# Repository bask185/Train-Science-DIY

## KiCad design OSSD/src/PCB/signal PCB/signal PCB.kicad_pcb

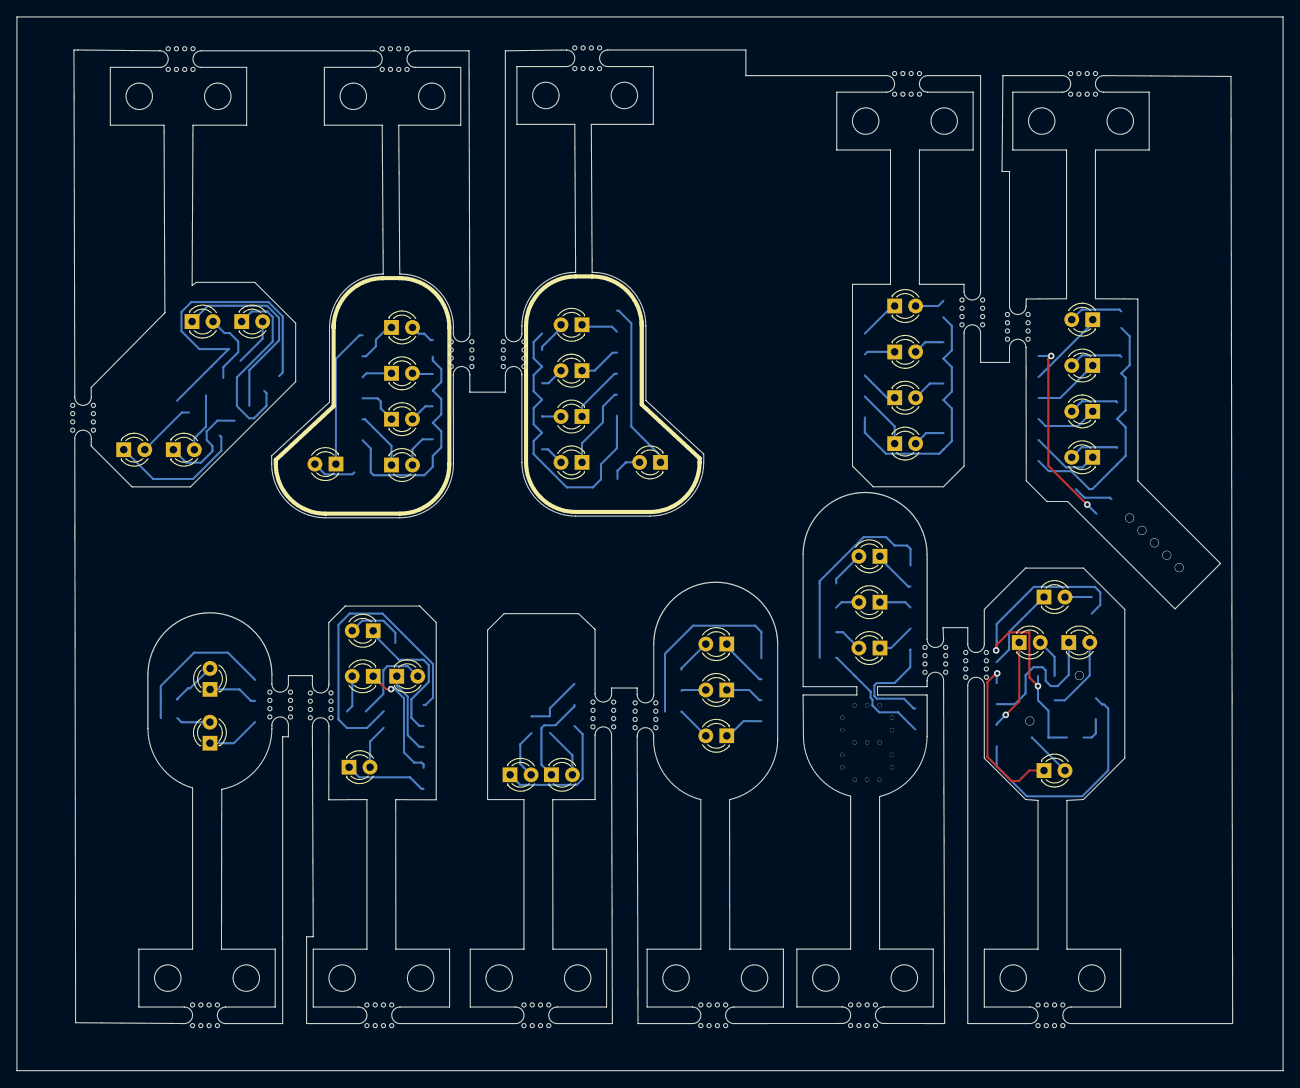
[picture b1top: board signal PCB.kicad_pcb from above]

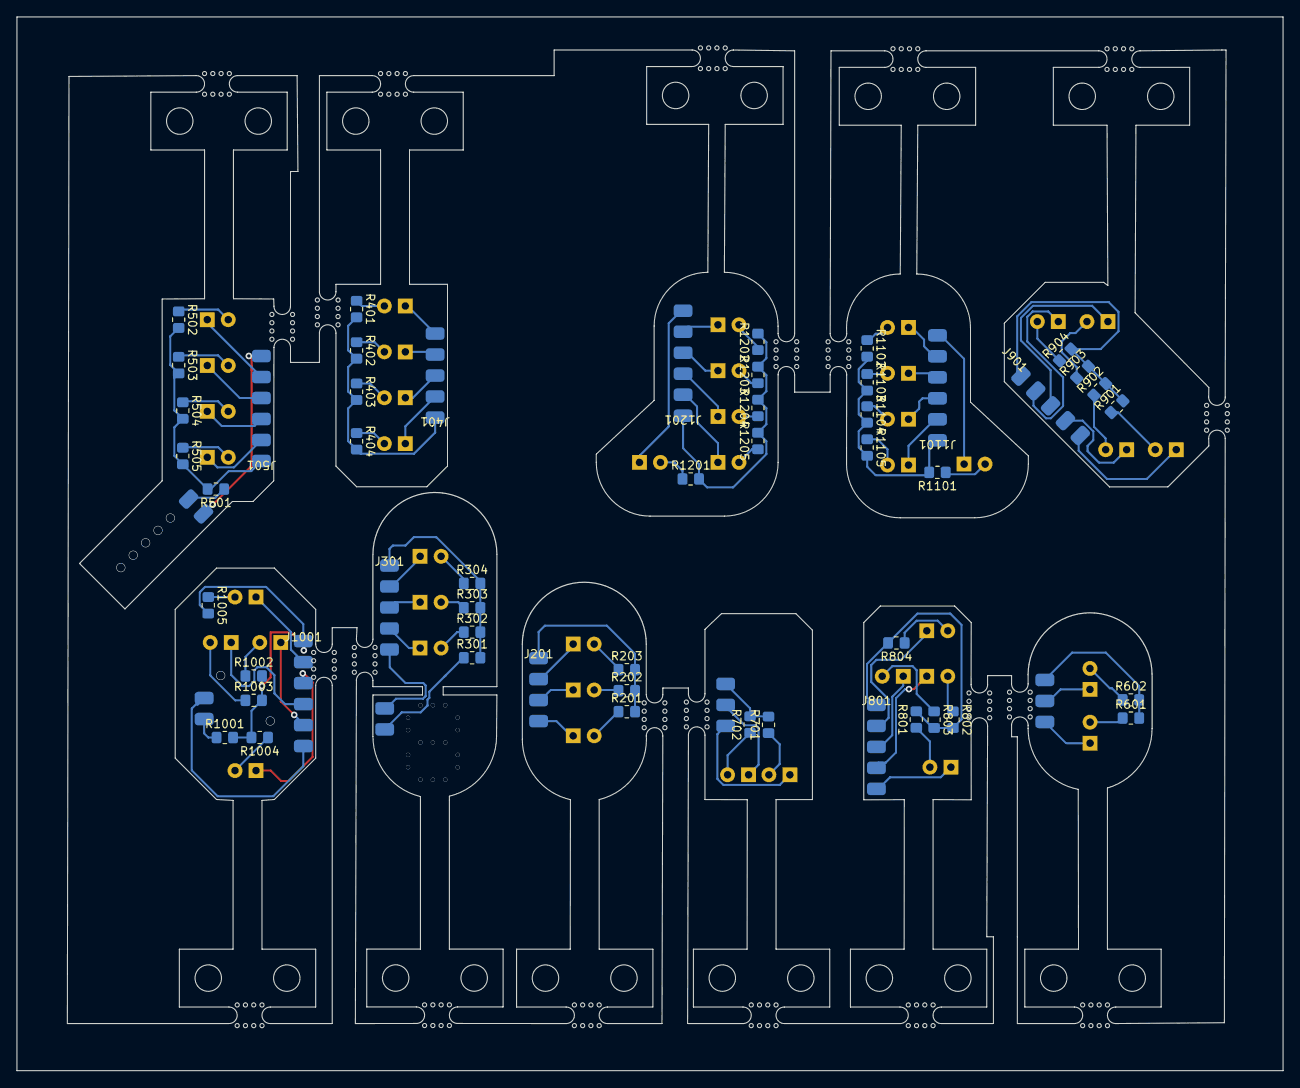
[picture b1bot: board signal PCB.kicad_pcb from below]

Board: 2 copper layers, 153.2 x 127.5 mm, 97 parts (57 on the bottom side), 97 nets.

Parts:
D201, D202, D203, D301, D302, D303, D401, D402, D403, D404, D501, D502, D503, D504, D601, D602, D701, D702, D801, D802, D803, D804, D901, D902, D903, D904, D1001, D1002, D1003, D1004, D1101, D1102, D1103, D1104, D1105, D1201, D1202, D1203, D1204, D1205: LED; LED_NO_SILK
D304, D505, D1005: LED; 02_solderpad_2.54
J201: Conn_01x04; 04_solderpad_2.54
J301, J401, J901: Conn_01x05; 05_solderpad_2.54
J501, J1001, J1101, J1201: Conn_01x06; 06_solderpad_2.54
J601, J701: Conn_01x04; 03_solderpad_2.54
J801: Conn_01x04; 05_solderpad_2.54
R201, R202, R203, R301, R302, R303, R304, R401, R402, R403, R404, R501, R502, R503, R504, R505, R601, R602, R701, R702, R801, R802, R803, R804, R901, R902, R903, R904, R1001, R1002, R1003, R1004, R1005, R1101, R1102, R1103, R1104, R1105, R1201, R1202, R1203, R1204, R1205: R; R_0805_2012Metric_Pad1.20x1.40mm_HandSolder

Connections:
unnamed: D201.2 (A), R203.1
unnamed: D201.1 (K), J201.2
unnamed: D202.2 (A), R202.1
unnamed: D202.1 (K), J201.3
unnamed: D203.2 (A), R201.1
unnamed: D203.1 (K), J201.4
unnamed: D301.2 (A), R304.1
unnamed: D301.1 (K), J301.2
unnamed: D302.2 (A), R303.1
unnamed: D302.1 (K), J301.3
unnamed: D303.2 (A), R302.1
unnamed: D303.1 (K), J301.4
unnamed: D304.2 (A), R301.1
unnamed: D304.1 (K), J301.5
unnamed: D401.2 (A), R404.1
unnamed: D401.1 (K), J401.2
unnamed: D402.2 (A), R403.1
unnamed: D402.1 (K), J401.3
unnamed: D403.2 (A), R402.1
unnamed: D403.1 (K), J401.4
unnamed: D404.2 (A), R401.1
unnamed: D404.1 (K), J401.5
unnamed: D501.2 (A), R505.1
unnamed: D501.1 (K), J501.2
unnamed: D502.2 (A), R504.1
unnamed: D502.1 (K), J501.3
unnamed: D503.2 (A), R503.1
unnamed: D503.1 (K), J501.4
unnamed: D504.2 (A), R502.1
unnamed: D504.1 (K), J501.5
unnamed: D505.2 (A), R501.1
unnamed: D505.1 (K), J501.6
unnamed: D601.2 (A), R602.1
unnamed: D601.1 (K), J601.2
unnamed: D602.2 (A), R601.1
unnamed: D602.1 (K), J601.3
unnamed: D701.2 (A), R702.1
unnamed: D701.1 (K), J701.2
unnamed: D702.2 (A), R701.1
unnamed: D702.1 (K), J701.3
unnamed: D801.2 (A), R804.1
unnamed: D801.1 (K), J801.2
unnamed: D802.2 (A), R803.1
unnamed: D802.1 (K), J801.3
unnamed: D803.2 (A), R802.1
unnamed: D803.1 (K), J801.4
unnamed: D804.2 (A), R801.1
unnamed: D804.1 (K), J801.5
unnamed: D901.2 (A), R904.1
unnamed: D901.1 (K), J901.2
unnamed: D902.2 (A), R903.1
unnamed: D902.1 (K), J901.3
unnamed: D903.2 (A), R902.1
unnamed: D903.1 (K), J901.4
unnamed: D904.2 (A), R901.1
unnamed: D904.1 (K), J901.5
unnamed: D1001.2 (A), R1005.1
unnamed: D1001.1 (K), J1001.2
unnamed: D1002.2 (A), R1004.1
unnamed: D1002.1 (K), J1001.3
unnamed: D1003.2 (A), R1003.1
unnamed: D1003.1 (K), J1001.4
unnamed: D1004.2 (A), R1002.1
unnamed: D1004.1 (K), J1001.5
unnamed: D1005.2 (A), R1001.1
unnamed: D1005.1 (K), J1001.6
unnamed: D1101.2 (A), R1105.1
unnamed: D1101.1 (K), J1101.2
unnamed: D1102.2 (A), R1104.1
unnamed: D1102.1 (K), J1101.3
unnamed: D1103.2 (A), R1103.1
unnamed: D1103.1 (K), J1101.4
unnamed: D1104.2 (A), R1102.1
unnamed: D1104.1 (K), J1101.5
unnamed: D1105.2 (A), R1101.1
unnamed: D1105.1 (K), J1101.6
unnamed: D1201.2 (A), R1205.1
unnamed: D1201.1 (K), J1201.2
unnamed: D1202.2 (A), R1204.1
unnamed: D1202.1 (K), J1201.3
unnamed: D1203.2 (A), R1203.1
unnamed: D1203.1 (K), J1201.4
unnamed: D1204.2 (A), R1202.1
unnamed: D1204.1 (K), J1201.5
unnamed: D1205.2 (A), R1201.1
unnamed: D1205.1 (K), J1201.6
unnamed: J201.1, R201.2, R202.2, R203.2
unnamed: J301.1, R301.2, R302.2, R303.2, R304.2
unnamed: J401.1, R401.2, R402.2, R403.2, R404.2
unnamed: J501.1, R501.2, R502.2, R503.2, R504.2, R505.2
unnamed: J601.1, R601.2, R602.2
unnamed: J701.1, R701.2, R702.2
unnamed: J801.1, R801.2, R802.2, R803.2, R804.2
unnamed: J901.1, R901.2, R902.2, R903.2, R904.2
unnamed: J1001.1, R1001.2, R1002.2, R1003.2, R1004.2, R1005.2
unnamed: J1101.1, R1101.2, R1102.2, R1103.2, R1104.2, R1105.2
unnamed: J1201.1, R1201.2, R1202.2, R1203.2, R1204.2, R1205.2

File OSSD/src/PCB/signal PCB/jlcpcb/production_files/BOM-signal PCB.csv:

Comment,Designator,Footprint,LCSC
LED,D505,02_solderpad_2.54,
LED,D1005,02_solderpad_2.54,
LED,D304,02_solderpad_2.54,
Conn_01x06,J1201,06_solderpad_2.54,
Conn_01x06,J1101,06_solderpad_2.54,
Conn_01x06,J1001,06_solderpad_2.54,
Conn_01x05,J901,05_solderpad_2.54,
Conn_01x04,J801,05_solderpad_2.54,
Conn_01x04,J701,03_solderpad_2.54,
Conn_01x04,J601,03_solderpad_2.54,
Conn_01x06,J501,06_solderpad_2.54,
Conn_01x05,J401,05_solderpad_2.54,
Conn_01x05,J301,05_solderpad_2.54,
Conn_01x04,J201,04_solderpad_2.54,
LED,D1101,LED_NO_SILK,
LED,D1001,LED_NO_SILK,
LED,D302,LED_NO_SILK,
LED,D402,LED_NO_SILK,
LED,D1102,LED_NO_SILK,
LED,D802,LED_NO_SILK,
LED,D602,LED_NO_SILK,
LED,D303,LED_NO_SILK,
LED,D901,LED_NO_SILK,
LED,D1204,LED_NO_SILK,
LED,D701,LED_NO_SILK,
LED,D401,LED_NO_SILK,
LED,D301,LED_NO_SILK,
LED,D904,LED_NO_SILK,
LED,D1201,LED_NO_SILK,
LED,D201,LED_NO_SILK,
LED,D702,LED_NO_SILK,
LED,D801,LED_NO_SILK,
LED,D404,LED_NO_SILK,
LED,D1203,LED_NO_SILK,
LED,D502,LED_NO_SILK,
LED,D403,LED_NO_SILK,
LED,D501,LED_NO_SILK,
LED,D1002,LED_NO_SILK,
LED,D203,LED_NO_SILK,
LED,D503,LED_NO_SILK,
LED,D803,LED_NO_SILK,
LED,D903,LED_NO_SILK,
LED,D1105,LED_NO_SILK,
LED,D804,LED_NO_SILK,
LED,D1103,LED_NO_SILK,
LED,D601,LED_NO_SILK,
LED,D1003,LED_NO_SILK,
LED,D1104,LED_NO_SILK,
LED,D902,LED_NO_SILK,
LED,D202,LED_NO_SILK,
LED,D1004,LED_NO_SILK,
LED,D504,LED_NO_SILK,
LED,D1202,LED_NO_SILK,
LED,D1205,LED_NO_SILK,
R,R1102,R_0805_2012Metric_Pad1.20x1.40mm_HandSolder,
R,R1205,R_0805_2012Metric_Pad1.20x1.40mm_HandSolder,
R,R1005,R_0805_2012Metric_Pad1.20x1.40mm_HandSolder,
R,R1105,R_0805_2012Metric_Pad1.20x1.40mm_HandSolder,
R,R301,R_0805_2012Metric_Pad1.20x1.40mm_HandSolder,
R,R503,R_0805_2012Metric_Pad1.20x1.40mm_HandSolder,
R,R1004,R_0805_2012Metric_Pad1.20x1.40mm_HandSolder,
R,R903,R_0805_2012Metric_Pad1.20x1.40mm_HandSolder,
R,R802,R_0805_2012Metric_Pad1.20x1.40mm_HandSolder,
R,R504,R_0805_2012Metric_Pad1.20x1.40mm_HandSolder,
R,R1001,R_0805_2012Metric_Pad1.20x1.40mm_HandSolder,
R,R1204,R_0805_2012Metric_Pad1.20x1.40mm_HandSolder,
R,R1201,R_0805_2012Metric_Pad1.20x1.40mm_HandSolder,
R,R202,R_0805_2012Metric_Pad1.20x1.40mm_HandSolder,
R,R501,R_0805_2012Metric_Pad1.20x1.40mm_HandSolder,
R,R1003,R_0805_2012Metric_Pad1.20x1.40mm_HandSolder,
R,R803,R_0805_2012Metric_Pad1.20x1.40mm_HandSolder,
R,R1101,R_0805_2012Metric_Pad1.20x1.40mm_HandSolder,
R,R404,R_0805_2012Metric_Pad1.20x1.40mm_HandSolder,
R,R505,R_0805_2012Metric_Pad1.20x1.40mm_HandSolder,
R,R402,R_0805_2012Metric_Pad1.20x1.40mm_HandSolder,
R,R203,R_0805_2012Metric_Pad1.20x1.40mm_HandSolder,
R,R303,R_0805_2012Metric_Pad1.20x1.40mm_HandSolder,
R,R701,R_0805_2012Metric_Pad1.20x1.40mm_HandSolder,
R,R904,R_0805_2012Metric_Pad1.20x1.40mm_HandSolder,
R,R304,R_0805_2012Metric_Pad1.20x1.40mm_HandSolder,
R,R302,R_0805_2012Metric_Pad1.20x1.40mm_HandSolder,
R,R1202,R_0805_2012Metric_Pad1.20x1.40mm_HandSolder,
R,R601,R_0805_2012Metric_Pad1.20x1.40mm_HandSolder,
R,R1103,R_0805_2012Metric_Pad1.20x1.40mm_HandSolder,
R,R403,R_0805_2012Metric_Pad1.20x1.40mm_HandSolder,
R,R201,R_0805_2012Metric_Pad1.20x1.40mm_HandSolder,
R,R902,R_0805_2012Metric_Pad1.20x1.40mm_HandSolder,
R,R901,R_0805_2012Metric_Pad1.20x1.40mm_HandSolder,
R,R801,R_0805_2012Metric_Pad1.20x1.40mm_HandSolder,
R,R1002,R_0805_2012Metric_Pad1.20x1.40mm_HandSolder,
R,R502,R_0805_2012Metric_Pad1.20x1.40mm_HandSolder,
R,R1203,R_0805_2012Metric_Pad1.20x1.40mm_HandSolder,
R,R602,R_0805_2012Metric_Pad1.20x1.40mm_HandSolder,
R,R804,R_0805_2012Metric_Pad1.20x1.40mm_HandSolder,
R,R702,R_0805_2012Metric_Pad1.20x1.40mm_HandSolder,
R,R401,R_0805_2012Metric_Pad1.20x1.40mm_HandSolder,
R,R1104,R_0805_2012Metric_Pad1.20x1.40mm_HandSolder,

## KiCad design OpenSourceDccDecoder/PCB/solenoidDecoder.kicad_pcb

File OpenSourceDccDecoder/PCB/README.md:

# Loconet and/or DCC servo decoder

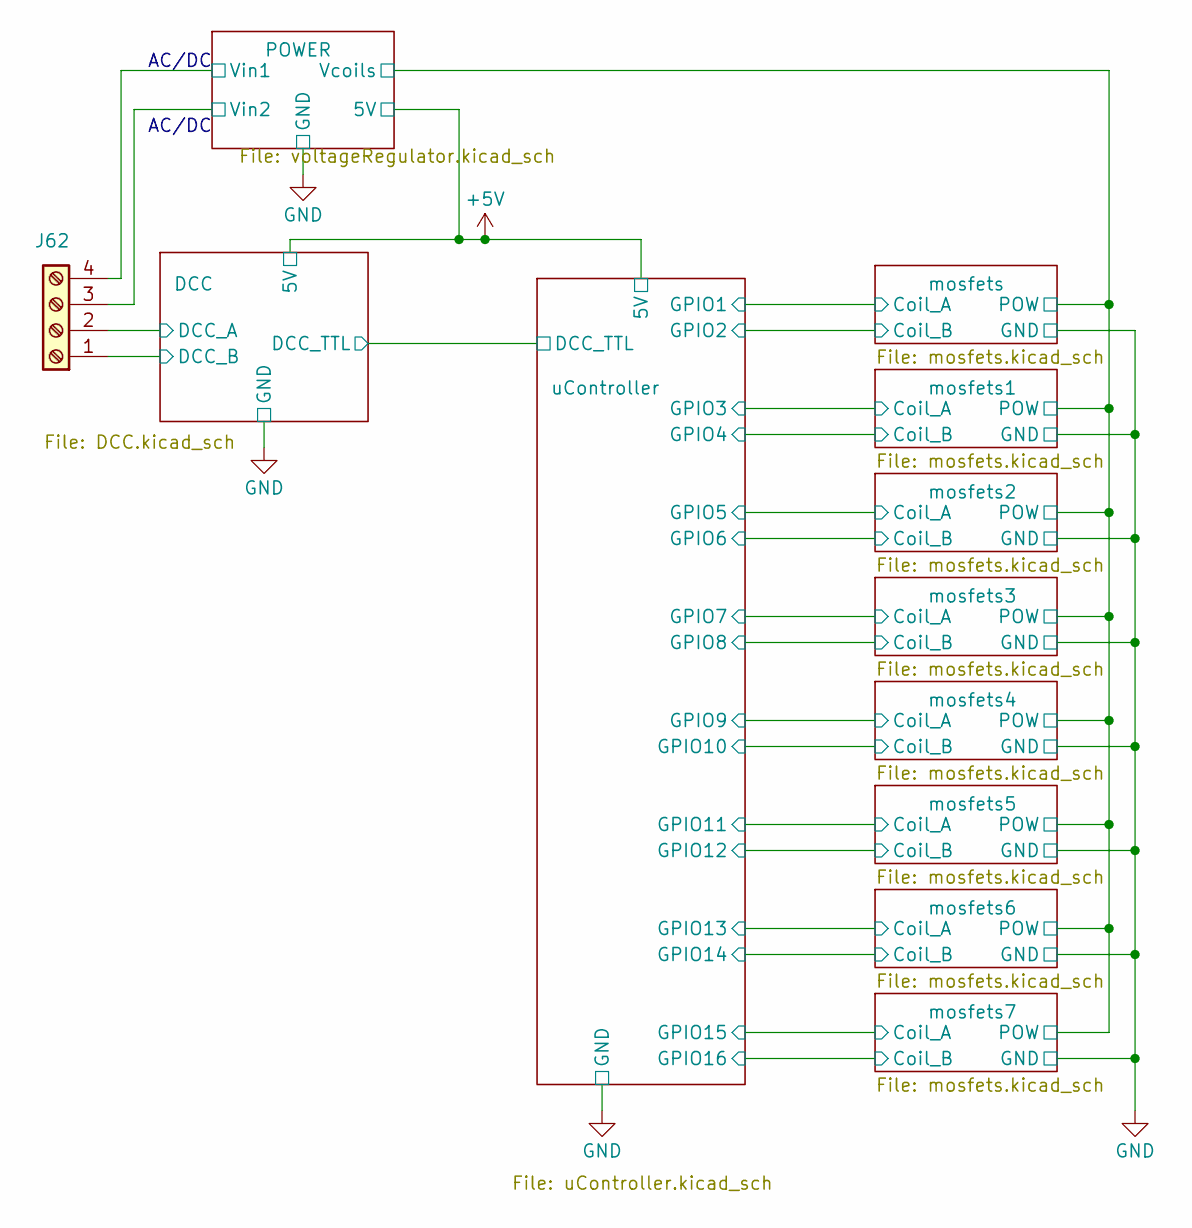
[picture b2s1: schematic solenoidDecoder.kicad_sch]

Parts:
J62: Screw_Terminal_01x04; TerminalBlock_Phoenix_MKDS-1,5-4-5.08_1x04_P5.08mm_Horizont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

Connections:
/DCC/DCC_A: J62.2; also elsewhere on the board
/DCC/DCC_B: J62.1; also elsewhere on the board
/POWER/Vin1: J62.4; also elsewhere on the board
/POWER/Vin2: J62.3; also elsewhere on the board

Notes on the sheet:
AC/DC

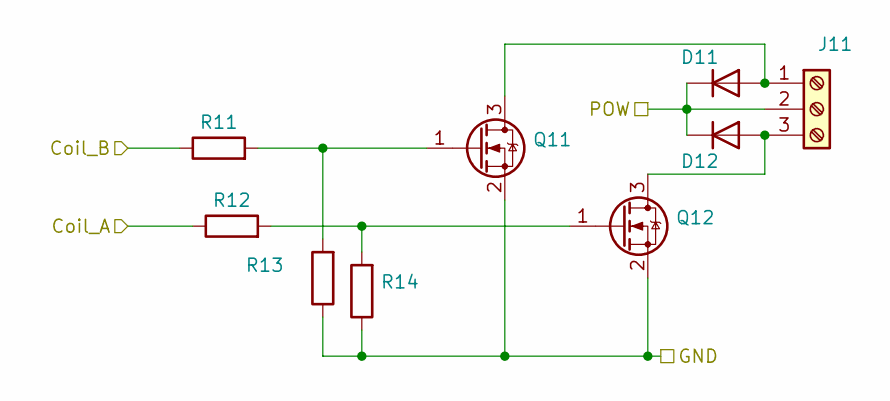
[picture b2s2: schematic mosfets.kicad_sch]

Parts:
D11, D12: D_SMA; JLCPCB Part# C8678
J11: TerminalBlock_Phoenix_MKDS-1,5-3-5.08_1x03_P5.08mm_Horizont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
Q11, Q12: SOT-23; JLCPCB Part# C20917
R11, R12: R_0603_1608Metric_Pad0.98x0.95mm_HandSolder; JLCPCB Part# C17958
R13, R14: R_0603_1608Metric_Pad0.98x0.95mm_HandSolder; JLCPCB Part# C17902

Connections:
/POWER/Vcoils: D11.1 (K), D12.1 (K), J11.2; also elsewhere on the board
/uController/GPIO1: R12.1; also elsewhere on the board
/uController/GPIO2: R11.1; also elsewhere on the board
GND: Q11.2 (S), Q12.2 (S), R13.1, R14.1; also elsewhere on the board
unnamed: D11.2 (A), J11.1, Q11.3 (D)
unnamed: D12.2 (A), J11.3, Q12.3 (D)
unnamed: Q11.1 (G), R11.2, R13.2
unnamed: Q12.1 (G), R12.2, R14.2

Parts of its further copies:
D21, D22, D31, D32, D41, D42, D51, D52, D61, D62, D71, D72, D81, D82: D_SMA; JLCPCB Part# C8678
J21, J31, J41, J51, J61, J71, J81: TerminalBlock_Phoenix_MKDS-1,5-3-5.08_1x03_P5.08mm_Horizont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
Q21, Q22, Q31, Q32, Q41, Q42, Q51, Q52, Q61, Q62, Q71, Q72, Q81, Q82: SOT-23; JLCPCB Part# C20917
R21, R22, R31, R32, R41, R42, R51, R52, R61, R62, R71, R72, R81, R82: R_0603_1608Metric_Pad0.98x0.95mm_HandSolder; JLCPCB Part# C17958
R23, R24, R33, R34, R43, R44, R53, R54, R63, R64, R73, R74, R83, R84: R_0603_1608Metric_Pad0.98x0.95mm_HandSolder; JLCPCB Part# C17902

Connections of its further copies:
/POWER/Vcoils: D21.1 (K), D22.1 (K), D31.1 (K), D32.1 (K), D41.1 (K), D42.1 (K), D51.1 (K), D52.1 (K), D61.1 (K), D62.1 (K), D71.1 (K), D72.1 (K), D81.1 (K), D82.1 (K), J21.2, J31.2, J41.2, J51.2, J61.2, J71.2, J81.2; also elsewhere on the board
/uController/GPIO3: R22.1; also elsewhere on the board
/uController/GPIO4: R21.1; also elsewhere on the board
/uController/GPIO9: R52.1; also elsewhere on the board
/uController/GPIO10: R51.1; also elsewhere on the board
/uController/GPIO11: R62.1; also elsewhere on the board
/uController/GPIO12: R61.1; also elsewhere on the board
/uController/GPIO13: R72.1; also elsewhere on the board
/uController/GPIO14: R71.1; also elsewhere on the board
/uController/GPIO15: R82.1; also elsewhere on the board
/uController/GPIO16: R81.1; also elsewhere on the board
GND: Q21.2 (S), Q22.2 (S), Q31.2 (S), Q32.2 (S), Q41.2 (S), Q42.2 (S), Q51.2 (S), Q52.2 (S), Q61.2 (S), Q62.2 (S), Q71.2 (S), Q72.2 (S), Q81.2 (S), Q82.2 (S), R23.1, R24.1, R33.1, R34.1, R43.1, R44.1, R53.1, R54.1, R63.1, R64.1, R73.1, R74.1, R83.1, R84.1; also elsewhere on the board
unnamed: D21.2 (A), J21.1, Q21.3 (D)
unnamed: D22.2 (A), J21.3, Q22.3 (D)
unnamed: D31.2 (A), J31.1, Q31.3 (D)
unnamed: D32.2 (A), J31.3, Q32.3 (D)
unnamed: D41.2 (A), J41.1, Q41.3 (D)
unnamed: D42.2 (A), J41.3, Q42.3 (D)
unnamed: D51.2 (A), J51.1, Q51.3 (D)
unnamed: D52.2 (A), J51.3, Q52.3 (D)
unnamed: D61.2 (A), J61.1, Q61.3 (D)
unnamed: D62.2 (A), J61.3, Q62.3 (D)
unnamed: D71.2 (A), J71.1, Q71.3 (D)
unnamed: D72.2 (A), J71.3, Q72.3 (D)
unnamed: D81.2 (A), J81.1, Q81.3 (D)
unnamed: D82.2 (A), J81.3, Q82.3 (D)
unnamed: Q21.1 (G), R21.2, R23.2
unnamed: Q22.1 (G), R22.2, R24.2
unnamed: Q31.1 (G), R31.2, R33.2
unnamed: Q32.1 (G), R32.2, R34.2
unnamed: Q41.1 (G), R41.2, R43.2
unnamed: Q42.1 (G), R42.2, R44.2
unnamed: Q51.1 (G), R51.2, R53.2
unnamed: Q52.1 (G), R52.2, R54.2
unnamed: Q61.1 (G), R61.2, R63.2
unnamed: Q62.1 (G), R62.2, R64.2
unnamed: Q71.1 (G), R71.2, R73.2
unnamed: Q72.1 (G), R72.2, R74.2
unnamed: Q81.1 (G), R81.2, R83.2
unnamed: Q82.1 (G), R82.2, R84.2

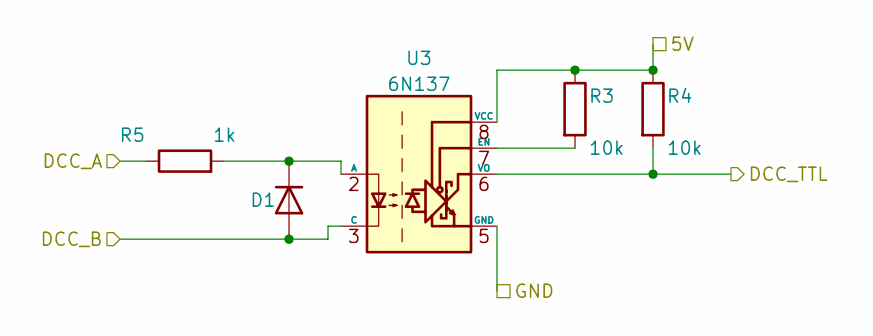
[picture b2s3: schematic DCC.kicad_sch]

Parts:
D1: D; D_SOD-323; JLCPCB Part# C2128
R3, R4: 10k; R_0805_2012Metric_Pad1.20x1.40mm_HandSolder; JLCPCB Part# C17414
R5: 1k; R_0805_2012Metric_Pad1.20x1.40mm_HandSolder; JLCPCB Part# C17513
U3: 6N137; SOP-8_6.62x9.15mm_P2.54mm; JLCPCB Part# C110020

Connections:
+5V: R3.1, R4.1, U3.8 (VCC); also elsewhere on the board
/DCC/DCC_A: R5.1; also elsewhere on the board
/DCC/DCC_B: D1.2 (A), U3.3 (C); also elsewhere on the board
/DCC/DCC_TTL: R4.2, U3.6 (VO); also elsewhere on the board
GND: U3.5 (GND); also elsewhere on the board
unnamed: D1.1 (K), R5.2, U3.2 (A)
unnamed: R3.2, U3.7 (EN)

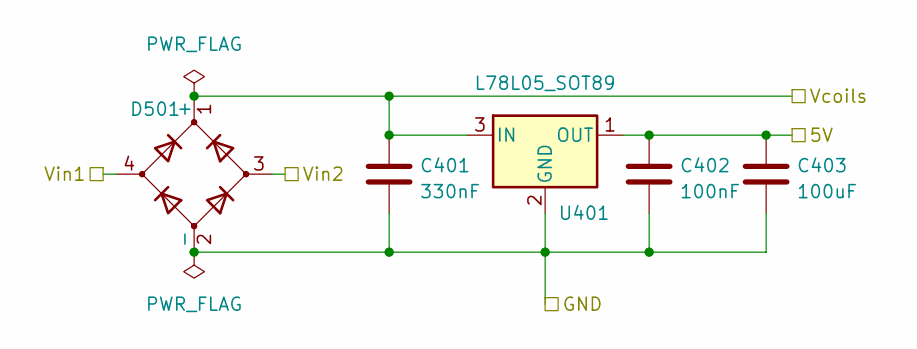
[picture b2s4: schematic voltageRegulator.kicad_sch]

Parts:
C401: 330nF; C_0603_1608Metric_Pad1.08x0.95mm_HandSolder; JLCPCB Part# C1615
C402: 100nF; C_0603_1608Metric_Pad1.08x0.95mm_HandSolder; JLCPCB Part# C14663
C403: 100uF; C_1206_3216Metric_Pad1.33x1.80mm_HandSolder; JLCPCB Part# C15008
D501: Diode_Bridge_Diotec_SO-DIL-Slim; JLCPCB Part# C2826463
U401: L78L05_SOT89; SOT-89-3; JLCPCB Part# C71136

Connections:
+5V: C402.1, C403.1, U401.1 (OUT); also elsewhere on the board
/POWER/Vcoils: C401.1, U401.3 (IN); also elsewhere on the board
GND: C401.2, C402.2, C403.2, U401.2 (GND); also elsewhere on the board

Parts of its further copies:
D2: Diode_Bridge_Diotec_SO-DIL-Slim; JLCPCB Part# C2826463

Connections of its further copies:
/POWER/Vcoils: D2.1 (+); also elsewhere on the board
/POWER/Vin1: D2.4; also elsewhere on the board
/POWER/Vin2: D2.3; also elsewhere on the board
GND: D2.2 (-); also elsewhere on the board

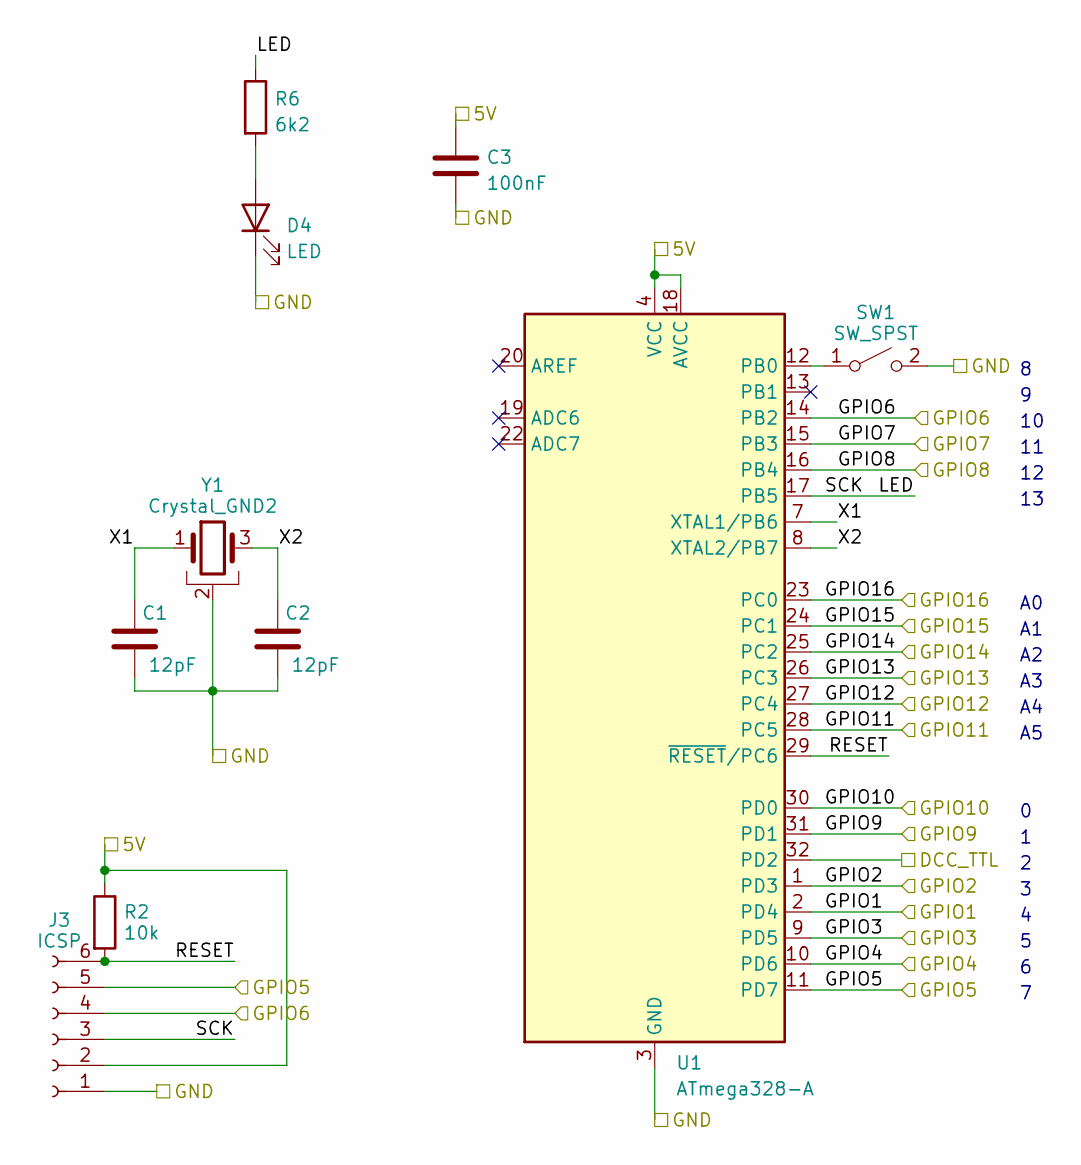
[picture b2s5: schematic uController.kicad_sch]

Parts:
C1, C2: 12pF; C_0402_1005Metric_Pad0.74x0.62mm_HandSolder; JLCPCB Part# C1547
C3: 100nF; C_0603_1608Metric_Pad1.08x0.95mm_HandSolder; JLCPCB Part# C14663
D4: LED; LED_0805_2012Metric_Pad1.15x1.40mm_HandSolder; JLCPCB Part# C84256
J3: ICSP; PinHeader_1x06_P2.54mm_Vertical
R2: 10k; R_0402_1005Metric_Pad0.72x0.64mm_HandSolder; JLCPCB Part# C25744
R6: 6k2; R_0603_1608Metric_Pad0.98x0.95mm_HandSolder; JLCPCB Part# C4260
SW1: SW_SPST; SW_SPST_SKQG_WithStem; JLCPCB Part# C318884
U1: ATmega328-A; TQFP-32_7x7mm_P0.8mm; JLCPCB Part# C14877
Y1: Crystal_GND2; crystal_arduino

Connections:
+5V: C3.2, J3.2, R2.1, U1.4 (VCC), U1.6 (VCC), U1.18 (AVCC); also elsewhere on the board
/DCC/DCC_TTL: U1.32 (PD2); also elsewhere on the board
/uController/GPIO1: U1.2 (PD4); also elsewhere on the board
/uController/GPIO2: U1.1 (PD3); also elsewhere on the board
/uController/GPIO3: U1.9 (PD5); also elsewhere on the board
/uController/GPIO4: U1.10 (PD6); also elsewhere on the board
/uController/GPIO9: U1.31 (PD1); also elsewhere on the board
/uController/GPIO10: U1.30 (PD0); also elsewhere on the board
/uController/GPIO11: U1.28 (PC5); also elsewhere on the board
/uController/GPIO12: U1.27 (PC4); also elsewhere on the board
/uController/GPIO13: U1.26 (PC3); also elsewhere on the board
/uController/GPIO14: U1.25 (PC2); also elsewhere on the board
/uController/GPIO15: U1.24 (PC1); also elsewhere on the board
/uController/GPIO16: U1.23 (PC0); also elsewhere on the board
/uController/LED: J3.3, R6.1, U1.17 (PB5)
/uController/RESET: J3.6, R2.2, U1.29 (~RESET/PC6)
/uController/X1: C1.2, U1.7 (XTAL1/PB6), Y1.1
/uController/X2: C2.2, U1.8 (XTAL2/PB7), Y1.3
GND: C1.1, C2.1, C3.1, D4.1 (K), J3.1, SW1.2 (B), U1.3 (GND), U1.5 (GND), U1.21 (GND), Y1.2 (GND), Y1.4 (GND); also elsewhere on the board
unnamed: D4.2 (A), R6.2
unnamed: SW1.1 (A), U1.12 (PB0)

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
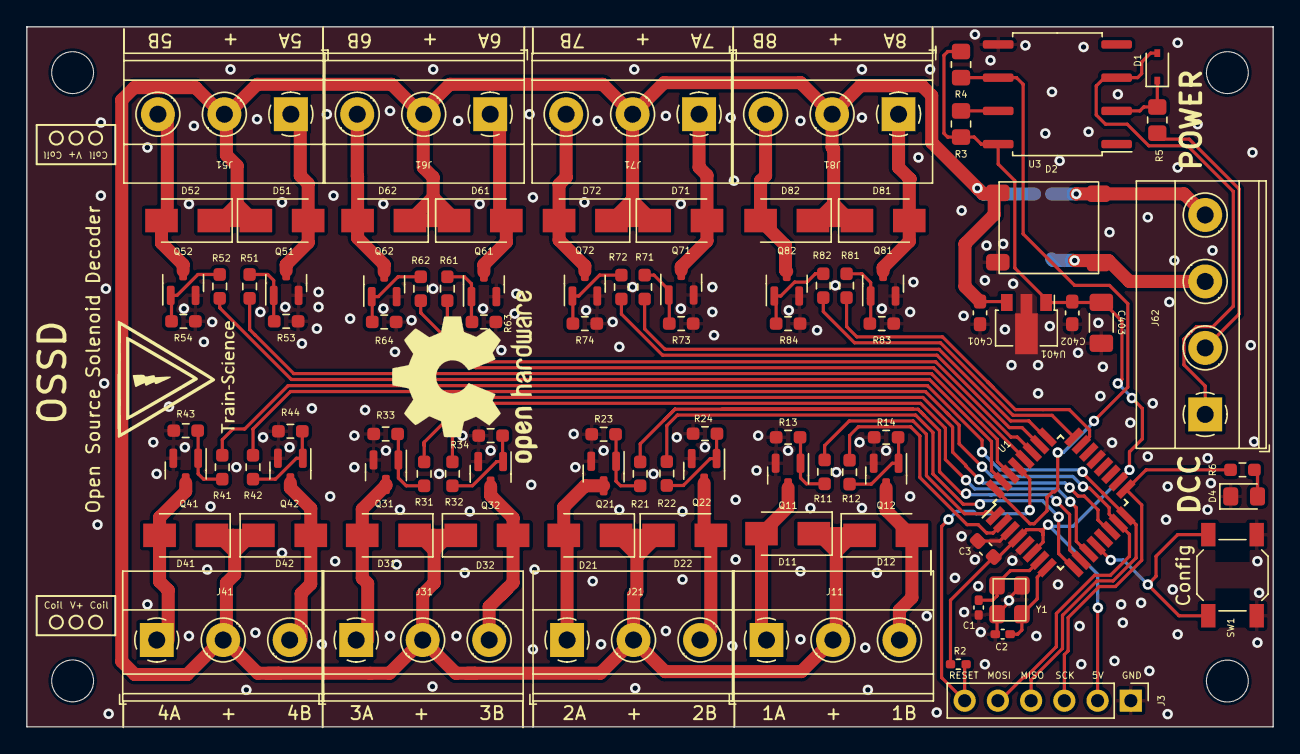
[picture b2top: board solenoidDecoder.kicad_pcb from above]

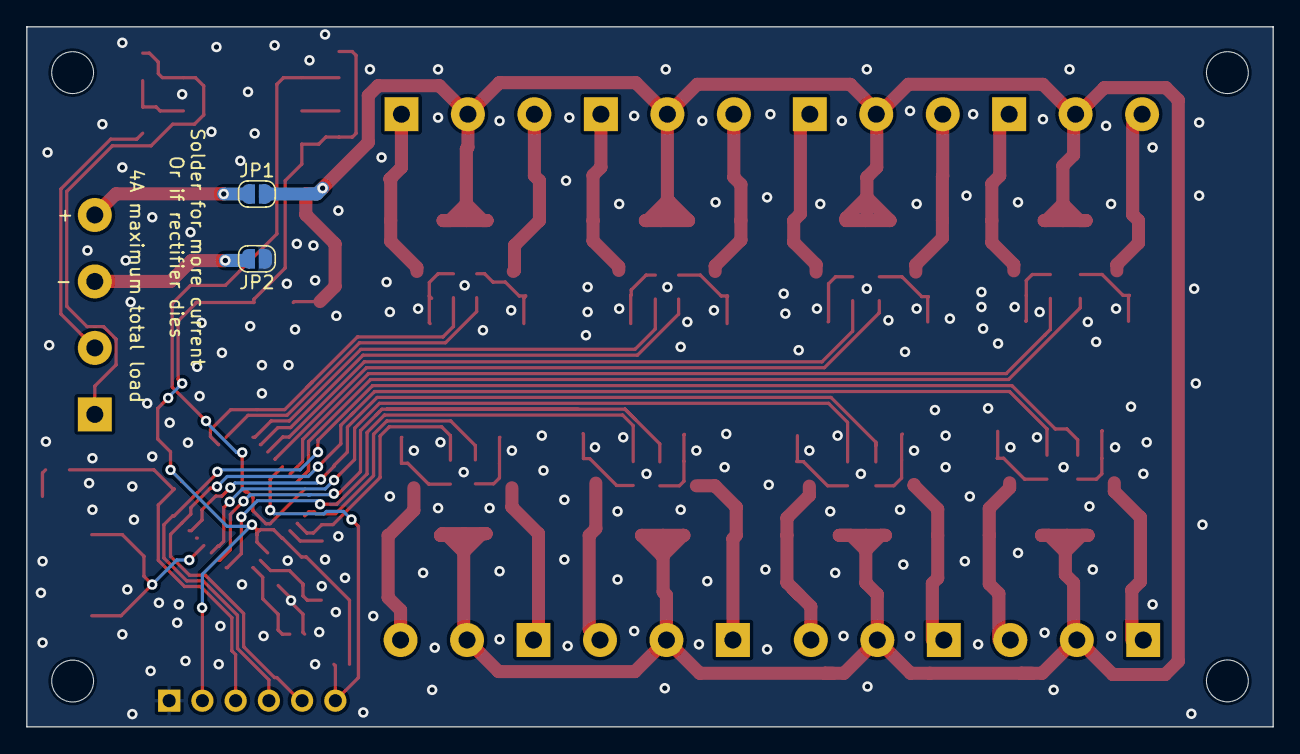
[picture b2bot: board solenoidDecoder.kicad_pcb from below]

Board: 2 copper layers, 95.3 x 53.5 mm, 95 parts (2 on the bottom side), 64 nets.

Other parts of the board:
JP1, JP2: SolderJumper_2_Open; SolderJumper-2_P1.3mm_Open_RoundedPad1.0x1.5mm

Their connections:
/POWER/Vcoils: JP1.2 (B); also elsewhere on the board
/POWER/Vin1: JP1.1 (A); also elsewhere on the board
/POWER/Vin2: JP2.2 (B); also elsewhere on the board
GND: JP2.1 (A); also elsewhere on the board

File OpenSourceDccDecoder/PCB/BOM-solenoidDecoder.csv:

Comment,Designator,Footprint,LCSC
6N137,U3,SOP-8_6.62x9.15mm_P2.54mm,C110020
100nF,"C3,C402",C_0603_1608Metric_Pad1.08x0.95mm_HandSolder,C14663
ATmega328-A,U1,TQFP-32_7x7mm_P0.8mm,C14877
100uF,C403,C_1206_3216Metric_Pad1.33x1.80mm_HandSolder,C15008
12pF,"C1,C2",C_0402_1005Metric_Pad0.74x0.62mm_HandSolder,C1547
330nF,C401,C_0603_1608Metric_Pad1.08x0.95mm_HandSolder,C1615
~,D2,4A rectifier,C169511
10k,"R3,R4",R_0805_2012Metric_Pad1.20x1.40mm_HandSolder,C17414
1k,R5,R_0805_2012Metric_Pad1.20x1.40mm_HandSolder,C17513
~,"Q11,Q12,Q21,Q22,Q31,Q32,Q41,Q42,Q51,Q52,Q61,Q62,Q71,Q72,Q81,Q82",SOT-23,C20917
D,D1,D_SOD-323,C2128
~,"R11,R12,R21,R22,R31,R32,R41,R42,R51,R52,R61,R62,R71,R72,R81,R82",R_0603_1608Metric_Pad0.98x0.95mm_HandSolder,C23345
10k,R2,R_0402_1005Metric_Pad0.72x0.64mm_HandSolder,C25744
~,"R13,R14,R23,R24,R33,R34,R43,R44,R53,R54,R63,R64,R73,R74,R83,R84",R_0603_1608Metric_Pad0.98x0.95mm_HandSolder,C25804
SW_SPST,SW1,SW_SPST_SKQG_WithStem,C318884
6k2,R6,R_0603_1608Metric_Pad0.98x0.95mm_HandSolder,C4260
L78L05_SOT89,U401,SOT-89-3,C71136
LED,D4,LED_0805_2012Metric_Pad1.15x1.40mm_HandSolder,C84256
~,"D11,D12,D21,D22,D31,D32,D41,D42,D51,D52,D61,D62,D71,D72,D81,D82",D_SMA,C8678
SolderJumper_2_Open,JP2,SolderJumper-2_P1.3mm_Open_RoundedPad1.0x1.5mm,
SolderJumper_2_Open,JP1,SolderJumper-2_P1.3mm_Open_RoundedPad1.0x1.5mm,
Screw_Terminal_01x04,J62,"TerminalBlock_Phoenix_MKDS-1,5-4-5.08_1x04_P5.08mm_Horizontal",
~,J41,"TerminalBlock_Phoenix_MKDS-1,5-3-5.08_1x03_P5.08mm_Horizontal",
ICSP,J3,PinHeader_1x06_P2.54mm_Vertical,
Crystal_GND2,Y1,crystal_arduino,
~,J81,"TerminalBlock_Phoenix_MKDS-1,5-3-5.08_1x03_P5.08mm_Horizontal",
~,J61,"TerminalBlock_Phoenix_MKDS-1,5-3-5.08_1x03_P5.08mm_Horizontal",
~,J51,"TerminalBlock_Phoenix_MKDS-1,5-3-5.08_1x03_P5.08mm_Horizontal",
~,J31,"TerminalBlock_Phoenix_MKDS-1,5-3-5.08_1x03_P5.08mm_Horizontal",
~,J21,"TerminalBlock_Phoenix_MKDS-1,5-3-5.08_1x03_P5.08mm_Horizontal",
~,J71,"TerminalBlock_Phoenix_MKDS-1,5-3-5.08_1x03_P5.08mm_Horizontal",
~,J11,"TerminalBlock_Phoenix_MKDS-1,5-3-5.08_1x03_P5.08mm_Horizontal",

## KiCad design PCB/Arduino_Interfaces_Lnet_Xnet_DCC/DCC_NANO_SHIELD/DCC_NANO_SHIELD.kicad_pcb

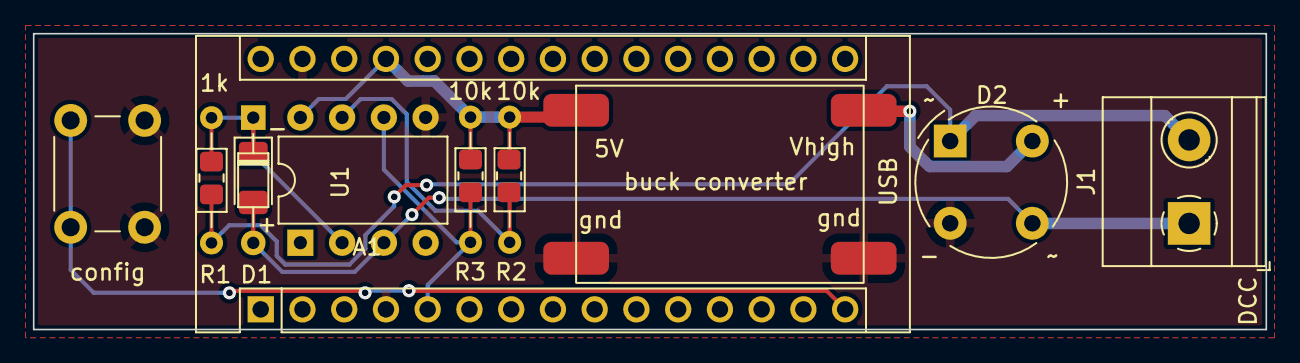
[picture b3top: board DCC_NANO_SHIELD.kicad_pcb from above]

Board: 2 copper layers, 75.0 x 18.0 mm, 14 parts (0 on the bottom side), 9 nets.

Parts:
A1: Arduino_Nano_v3.x; Arduino_Nano
D1: D; D_DO-34_SOD68_P7.62mm_Horizontal
D2: D_Bridge_+A-A; Diode_Bridge_Round_D9.0mm
D11: D; D_1206_3216Metric_Pad1.42x1.75mm_HandSolder
J1: Screw_Terminal_01x02; TerminalBlock_Phoenix_MKDS-1,5-2-5.08_1x02_P5.08mm_Horizont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
R1: 1k; R_Axial_DIN0204_L3.6mm_D1.6mm_P7.62mm_Horizontal
R2, R3: 10k; R_Axial_DIN0204_L3.6mm_D1.6mm_P7.62mm_Horizontal
R11: 1k; R_0805_2012Metric_Pad1.20x1.40mm_HandSolder
R21, R31: 10k; R_0805_2012Metric_Pad1.20x1.40mm_HandSolder
SW1: config; SW_PUSH_6mm
U1: 6N137; DIP-8_W7.62mm
U2: Buck

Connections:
+5V: A1.27 (+5V), R2.1, R3.1, R21.1, R31.1, U1.8 (VCC), U2.1 (5V)
/DCC: A1.5 (D2), R3.2, R31.2, U1.6 (VO)
/DCC_A: D2.1 (+), J1.2, R1.1, R11.1
/DCC_B: D1.2 (A), D2.3 (-), D11.2 (A), J1.1, U1.3 (C)
GND: A1.4 (GND), A1.29 (GND), D2.2, SW1.2 (B), U1.5 (GND), U2.2 (gnd), U2.3 (gnd)
unnamed: A1.15 (D12), SW1.1 (A)
unnamed: D1.1 (K), D11.1 (K), R1.2, R11.2, U1.2 (A)
unnamed: D2.4, U2.4 (in+)
unnamed: R2.2, R21.2, U1.7 (EN)

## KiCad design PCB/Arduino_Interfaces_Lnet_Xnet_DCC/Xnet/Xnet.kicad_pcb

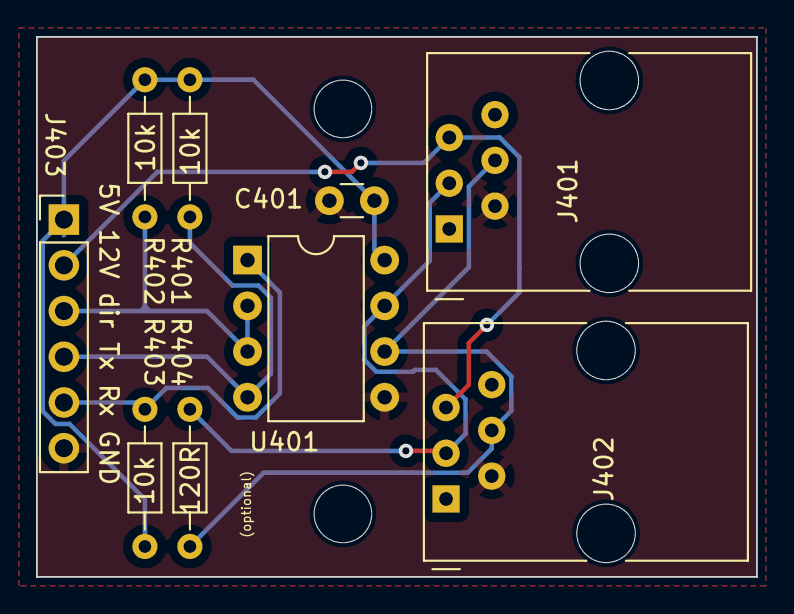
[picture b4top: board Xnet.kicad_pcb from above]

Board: 2 copper layers, 40.0 x 30.0 mm, 9 parts (0 on the bottom side), 8 nets.

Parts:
C401: 100n; C_Disc_D3.0mm_W1.6mm_P2.50mm
J401, J402: RJ12; RJ12_Amphenol_54601
J403: Conn_01x06_Male; PinHeader_1x06_P2.54mm_Vertical
R401, R402, R403: 10k; R_Axial_DIN0204_L3.6mm_D1.6mm_P7.62mm_Horizontal
R404: 120R; R_Axial_DIN0204_L3.6mm_D1.6mm_P7.62mm_Horizontal
U401: MAX485E; DIP-8_W7.62mm

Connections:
+5V: C401.1, J403.1, R401.2, R402.2, R403.2, U401.8 (VCC)
+12V: J401.5, J402.5, J403.2
/Xnet/A: J401.4, J402.4, R404.1, U401.6 (A)
/Xnet/B: J401.3, J402.3, R404.2, U401.7 (B)
GND: C401.2, J401.2, J402.2, J403.6, U401.5 (GND)
Rx: J403.5, R403.1, U401.1 (RO)
Tx: J403.4, R401.1, U401.4 (DI)
dir: J403.3, R402.1, U401.2 (~RE), U401.3 (DE)

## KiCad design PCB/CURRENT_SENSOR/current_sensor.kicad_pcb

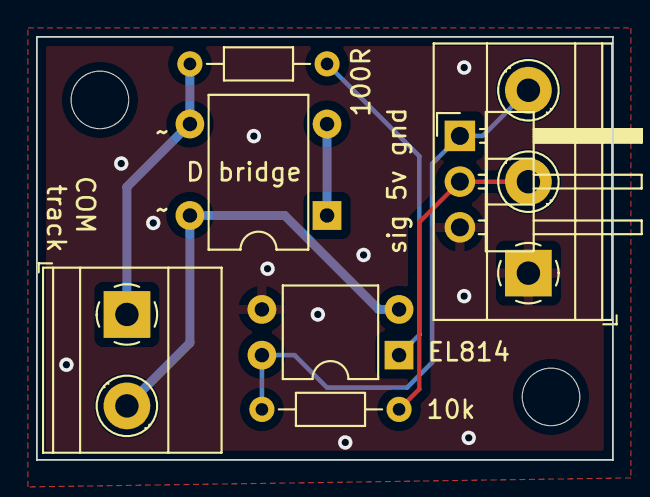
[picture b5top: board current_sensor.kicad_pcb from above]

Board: 2 copper layers, 32.0 x 23.5 mm, 7 parts (0 on the bottom side), 7 nets.

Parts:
D1201: D; Diode_Bridge_DIP-4_W7.62mm_P5.08mm
J1201: tracks; TerminalBlock_Phoenix_MKDS-1,5-2-5.08_1x02_P5.08mm_Horizont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
J1202: ter; TerminalBlock_Phoenix_MKDS-1,5-3-5.08_1x03_P5.08mm_Horizont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
J1203: ter; PinHeader_1x03_P2.54mm_Horizontal
R1201: 100R; R_Axial_DIN0204_L3.6mm_D1.6mm_P7.62mm_Horizontal
R1202: 10k; R_Axial_DIN0204_L3.6mm_D1.6mm_P7.62mm_Horizontal
U1201: EL814; DIP-4_W7.62mm

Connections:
+5V: J1202.2, J1203.2, R1202.1
GND: J1202.1, J1203.3, U1201.3
unnamed: D1201.1 (+), D1201.2 (-)
unnamed: D1201.3, J1201.1, R1201.1
unnamed: D1201.4, J1201.2, U1201.2
unnamed: R1201.2, U1201.1
sig: J1202.3, J1203.1, R1202.2, U1201.4
